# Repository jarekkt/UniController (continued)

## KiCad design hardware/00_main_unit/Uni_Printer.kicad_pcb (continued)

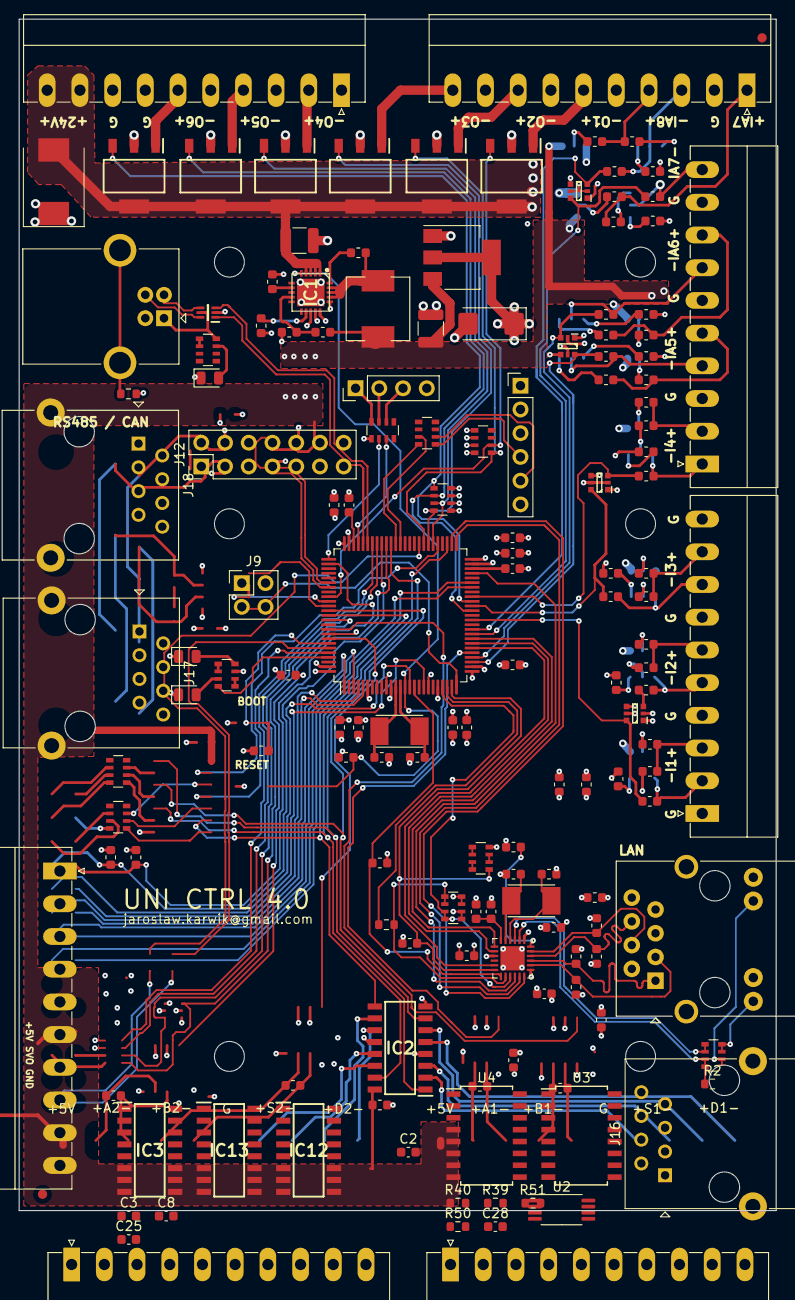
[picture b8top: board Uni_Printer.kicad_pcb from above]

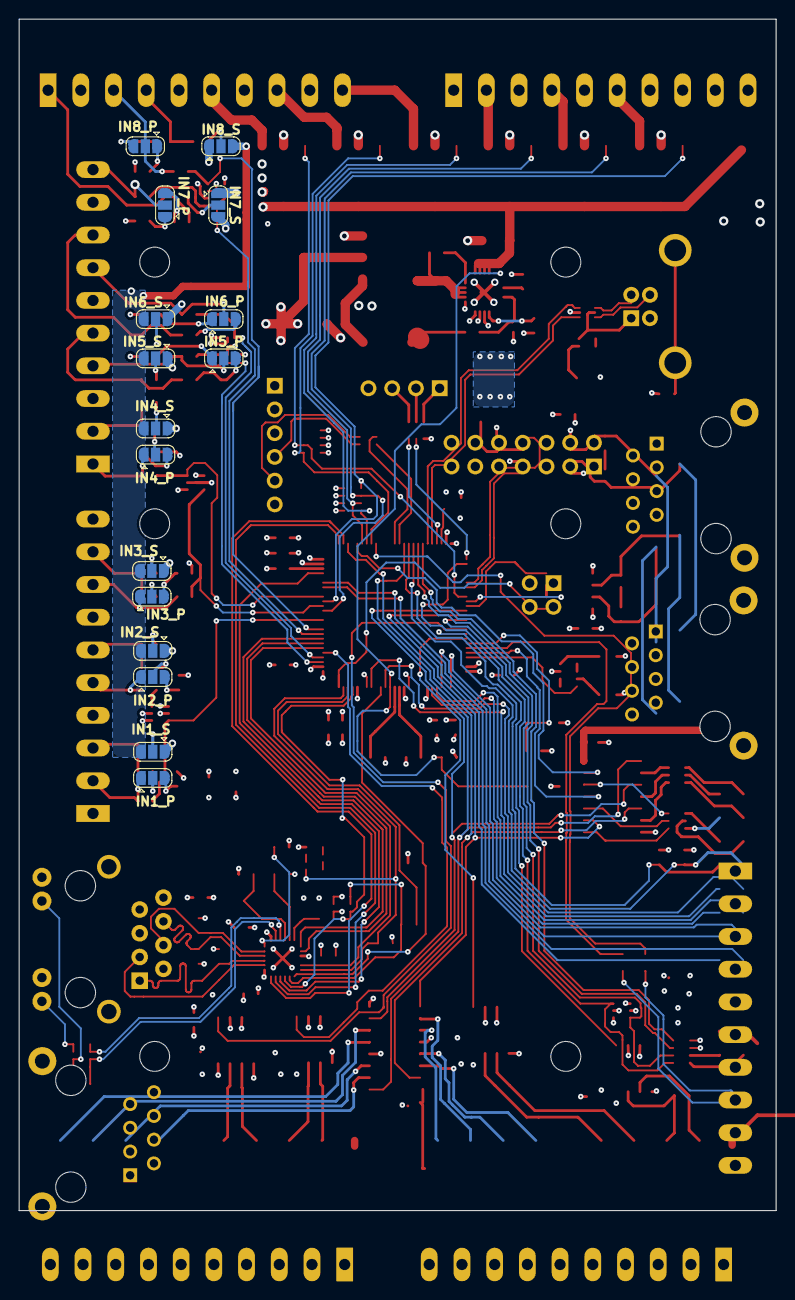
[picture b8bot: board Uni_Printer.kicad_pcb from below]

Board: 4 copper layers, 81.0 x 127.5 mm, 173 parts (16 on the bottom side), 202 nets.

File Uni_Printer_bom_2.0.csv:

Component,Description,Part,References,Value,Footprint,Quantity Per PCB,Datasheet,TME,Category,Mouser Price/Stock,Mouser Part Number,Manufacturer_Name,Height,RS Price/Stock,RS Part Number,Manufacturer_Part_Number,Arrow Part Number,Arrow Price/Stock,TME-WTYK,TME-GNIAZDO,Digi,MFG num
1,,C-Device,C4 C5 C18 C19,18pF,C_0603_1608Metric,4,~,VJ0603A180JXACW2BC,,,,,,,,,,,,,,
2,Unpolarized capacitor,C,C6 C7,18p,C_0603_1608Metric,2,~,,,,,,,,,,,,,,,
3,"Unpolarized capacitor, small symbol",C_Small,C42,5.6nF,C_0603_1608Metric,1,~,,,,,,,,,,,,,,,
4,"Unpolarized capacitor, small symbol",C_Small,C1 C21 C33 C35 C36 C37,100nF,C_0603_1608Metric,6,~,,,,,,,,,,,,,,,
5,,C-Device,C12 C14 C15 C16 C17 C20 C22 C24 C26 C31,100n,C_0603_1608Metric,10,~,C0603C104K3RAC,,,,,,,,,,,,,,
6,,C,C2 C3,100n,C_0603_1608Metric,2,,,Capacitor,,,,,,,,,,,,,
7,,C_Small-Device,C25 C27 C28 C29 C30 C34,100n,C_0603_1608Metric,6,~,C0603C104K3RAC WF06P-120R-5%,,,,,,,,,,,,,,
8,,C_Small-Sensor_tank_v1-rescue-Uni_General_v1-rescue-Uni_Printer_v1-rescue,C32,100n,C_0603_1608Metric,1,,C0603C104K3RAC,,,,,,,,,,,,,,
9,"Unpolarized capacitor, small symbol",C_Small,C41,2.2uF,C_0603_1608Metric,1,~,,,,,,,,,,,,,,,
10,,C-Device,C8 C10 C11 C13 C23 C38,10uF,C_1206_3216Metric,6,~,0805X106K100CT,,,,,,,,,,,,,,
11,"Unpolarized capacitor, small symbol",C_Small,C9,10uF,C_0603_1608Metric,1,~,,,,,,,,,,,,,,,
12,"Unpolarized capacitor, small symbol",C_Small,C44,100uF 6.3V Tantal,CP_EIA-6032-28_Kemet-C,1,~,,,,,,,,,,,,,,,
13,"Unpolarized capacitor, small symbol",C_Small,C40,10uF 50V,C_1210_3225Metric,1,~,,,,,,,,,,,,,,,
14,"Unpolarized capacitor, small symbol",C_Small,C43,22uF 25V,C_1206_3216Metric,1,~,,,,,,,,,,,,,,,
15,"Polarized capacitor, US symbol",CP1,CP1,1.0uF/1.0ESR,C_0603_1608Metric,1,~,,,,,,,,,,,,,,,
16,"Polarized capacitor, US symbol",CP1,CP2,470pF,C_0603_1608Metric,1,~,,,,,,,,,,,,,,,
17,,D_Schottky_x4_BAV99S-RESCUE-step2cnc-Sensor_tank_v1-rescue-Uni_General_v1-rescue-Uni_Printer_v1-rescue,D1 D4 D5 D7 D8,D_Schottky_x4_BAV99S,SOT-363,5,,BAV99S.115,,,,,,,,,,,,,,
18,,LED-Sensor_tank_v1-rescue-Uni_General_v1-rescue-Uni_Printer_v1-rescue,D2 D3 D9,LED,LED_0805_2012Metric,3,,,,,,,,,,,,,,,,
19,,NUF2042XV6T1G,D6,NUF2042XV6T1G,SOT50P160X60-6N,1,~,,,,,,,,,,,,,,,
20,Bidirectional transient-voltage-suppression diode,D_TVS,D10,SMCJ24CA,D_SMC,1,~,SMCJ24CA,,,,,,,,,,,,,,
21,,74*14-step2cnc-Uni_Printer_v1-rescue,IC3,74HC14D,SO14,1,~,,,,,,,,,,,,,,,
22,,AM26C31CD-AM26C31CD-Uni_Printer_v1-rescue,IC2,AM26C31CD,SOIC127P600X175-16N,1,http://www.ti.com/lit/ds/symlink/am26c31.pdf,,,https://www.mouser.com/Search/Refine.aspx?Keyword=595-AM26C31CD,595-AM26C31CD,Texas Instruments,1.75,http://uk.rs-online.com/web/p/products/5170520P,5170520P,AM26C31CD,,,,,,
23,,ITS4141NHUMA1,IC6 IC7 IC8 IC9 IC10 IC11,ITS4141NHUMA1,SOT230P700X170-4N,6,http://www.farnell.com/datasheets/8560http://www.infineon.co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,,,https://www.mouser.co.uk/ProductDetail/Infineon-Technologies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,726-ITS4141NHUMA1,Infineon,1.7,,,ITS4141NHUMA1,ITS4141NHUMA1,https://www.arrow.com/en/products/its4141nhuma1/infineon-tec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,,,,
24,,LAN8720A,IC5,LAN8742A,QFN-24-1EP_4x4mm_P0.5mm_EP2.6x2.6mm,1,,,,,,,,,,,,,,,,
25,,MAX17503ATP+,IC1,MAX17503ATP+,QFN50P400X400X80-21N,1,https://pdfserv.maximintegrated.com/en/ds/MAX17503.pdf,,,https://www.mouser.com/Search/Refine.aspx?Keyword=700-MAX175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,700-MAX17503ATP+,Maxim Integrated,0.8,,,MAX17503ATP+,,,,,,
26,,LM1117-step2cnc-Sensor_tank_v1-rescue-Uni_General_v1-rescue-Uni_Printer_v1-rescue-Uni_Printer-rescue,IC4,TLV1117-33,SOT-223-3_TabPin2,1,,TLV1117-33CDCYG3,,,,,,,,,,,,,,
27,"Generic connector, single row, 01x04, script generated (kicad-library-utils/schlib/autogen/connector/)",Conn_01x04_Male,J13,Conn_01x04_Male,PinHeader_1x04_P2.54mm_Vertical,1,~,,,,,,,,,,,,,,,
28,,Conn_01x10-Connector_Generic,J1 J2 J3 J4 J7 J8,Conn_01x10,PhoenixContact_MC-G_10x3.50mm_Angled,6,~,,,,,,,,,,,,15EDGK-3.5/10P,15EDGRC-3.5/10P,,
29,"Generic connector, double row, 02x14, odd/even pin numbering scheme (row 1 odd numbers, row 2 even numbers), script generated (kicad-library-utils/schlib/autogen/connector/)",Conn_02x14_Odd_Even,J14,Conn_02x13_Odd_Even,PinHeader_2x14_P2.54mm_Vertical,1,~,,,,,,,,,,,,,,,
30,,RJ45-TRANSFO_v2-rj12,J11,LMJ1998824110DL1T39J,LMJ1998824110DL1T39J,1,,RJ45-TRAFO-L,,,,,,,,,,,,,,
31,"RJ connector, 8P8C (8 positions 8 connected)",RJ45,J9 J12,RJ45,RJ45_Amphenol_54602-x08_Horizontal,2,~,,,,,,,,,,,,,,,
32,,USB_B-Connector,J10,USB B connector,USB_B_OST_USB-B1HSxx_Horizontal,1,~,TUEB4F2D0B,,,,,,,,,,,,,,
33,,Jumper_3_Bridged12-Jumper,JP1 JP2 JP3 JP4 JP7 JP8 JP9 JP10 JP11 JP12 JP13 JP14 JP15 JP16 JP17 JP18,Jumper,SolderJumper-3_P1.3mm_Bridged2Bar12_RoundedPad1.0x1.5mm,16,~,WF06P-120R-5%,,,,,,,,,,,,,,
34,,Jumper_NO_Small-Device,JP5 JP6,Jumper,SolderJumper-2_P1.3mm_Open_RoundedPad1.0x1.5mm,2,~,,,,,,,,,,,,,,,
35,,INDUCTOR_SMALL,L1,10uH,L_0603_1608Metric,1,,,,,,,,,,,,,,,,
36,"Inductor, small symbol",L_Small,L2,10uH,HPI0630,1,~,HPI0630-100,,,,,,,,,,,,,,
37,,R-Sensor_tank_v1-rescue-Uni_General_v1-rescue-Uni_Printer_v1-rescue,R49,0R,R_0603_1608Metric,1,~,WF06P-120R-5%,,,,,,,,,,,,,,
38,,R-RESCUE-step2cnc8_,R1,33,R_0603_1608Metric,1,~,,,,,,,,,,,,,,,
39,,R-RESCUE-step2cnc8_,R45 R46 R47 R48,49R9,R_0603_1608Metric,4,~,,,,,,,,,,,,,,,
40,,R-Sensor_tank_v1-rescue-Uni_General_v1-rescue-Uni_Printer_v1-rescue,R8 R12 R16 R20 R28 R32 R36 R39 R40 R43,120R,R_0603_1608Metric,10,,CRCW06030000Z0TABC WF06P-120R-5%,,,,,,,,,,,,,,
41,,R-Device,R22 R23 R24 R25,120R,R_0603_1608Metric,4,~,WF06P-120R-5%,,,,,,,,,,,,,,
42,,R-Sensor_tank_v1-rescue-Uni_General_v1-rescue-Uni_Printer_v1-rescue,R6 R10 R14 R18 R27 R31 R35 R42,1k,R_0603_1608Metric,8,,HP03-1K5% WF06P-120R-5%,,,,,,,,,,,,,,
43,,R-Device,R3 R4 R5,2k2,R_0603_1608Metric,3,~,HP03-2K25%,,,,,,,,,,,,,,
44,,R-Sensor_tank_v1-rescue-Uni_General_v1-rescue-Uni_Printer_v1-rescue,R7 R9 R11 R13 R15 R17 R19 R21 R26 R29 R30 R33 R34 R37 R41 R44,10k,R_0603_1608Metric,16,,SMD0603-680R-1% WF06P-120R-5%,,,,,,,,,,,,,,
45,,R-RESCUE-step2cnc8_,R38,12k1,R_0603_1608Metric,1,~,,,,,,,,,,,,,,,
46,"Resistor, small symbol",R_Small,R53,39k,R_0603_1608Metric,1,~,,,,,,,,,,,,,,,
47,"Resistor, small symbol",R_Small,R52,178k,R_0603_1608Metric,1,~,,,,,,,,,,,,,,,
48,,R_Pack04-Device,RN1 RN4 RN5 RN6 RN7 RN8 RN9,100R,R_Array_Convex_4x0603,7,~,DR1206-390K-4/8,,,,,,,,,,,,,,
49,"4 resistor network, parallel topology",R_Pack04,RN2,10k,R_Array_Convex_4x0603,1,~,,,,,,,,,,,,,,,
50,,R_Pack04-Device,RN12 RN13,15k,R_Array_Convex_4x0603,2,~,,,,,,,,,,,,,,,
51,"4 resistor network, parallel topology",R_Pack04,RN3 RN10,390R,R_Array_Convex_4x0603,2,~,,,,,,,,,,,,,,,
52,,SW_Push-Switch,SW2 SW3,SW_Push,SW_SPST_B3U-1000P,2,,B3U-1000PM,,,,,,,,,,,,,,
53,,ST1480ACDR-Sensor_tank_v1-rescue-Uni_General_v1-rescue-Uni_Printer_v1-rescue,U5 U6 U7 U8 U9,ST1480ACDR,SOIC-8_3.9x4.9mm_P1.27mm,5,,SP3077EEN-L SP3485EN-L,,,,,,,,,,,,,,
54,,STM32H743VITx,U1,STM32H743VITx,LQFP-100_14x14mm_P0.5mm,1,,,,,,,,,,,,,,,,
55,,TLE9251VSJ,U3,TLE9251VSJ,SOIC-8_3.9x4.9mm_P1.27mm,1,,,Driver,,,,,,,,,,,,TLE9251VSJXUMA1TR-ND,TLE9251VSJ
56,,Crystal-Device,Y2,ABM7-25.000MHZ-D2Y-T,XTAL500X320X130N_v2,1,~,ABM7-25.000MHZ-D2Y,,,,,,,,,,,,,,
57,,Crystal-Device,Y1,ABM7-8.000MHZ-D2Y-T,XTAL500X320X130N_v2,1,~,ABM7-8.000MHZ-D2Y,,,,,,,,,,,,,,





Component Groups:,57
Component Count:,171
Fitted Components:,171
Number of PCBs:,1
Total components:,171
Schematic Version:,2.0
Schematic Date:,2020-04-30
PCB Variant:,default
BoM Date:,14.01.2021 11:15:03
Schematic Source:,Uni_Printer.kicad_sch
KiCad Version:,Eeschema (5.99.0-7794-gffe7d2ea49)

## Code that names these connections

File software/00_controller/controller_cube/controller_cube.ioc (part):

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Mcu.Name=STM32H743VITx
Mcu.Package=LQFP100
Mcu.UserName=STM32H743VITx
PA0.GPIOParameters=PinState,GPIO_Label
PA0.GPIO_Label=ENET_RST
PA0.PinState=GPIO_PIN_SET
PA0.Signal=GPIO_Output
PA1.GPIOParameters=GPIO_Speed
PA1.GPIO_Speed=GPIO_SPEED_FREQ_VERY_HIGH
PA1.Mode=RMII
PA1.Signal=ETH_REF_CLK
PA10.Mode=Asynchronous
PA10.Signal=USART1_RX
PA11.GPIOParameters=GPIO_Label
PA11.GPIO_Label=IO_CPU7
PA11.Signal=GPIO_Input
PA12.GPIOParameters=GPIO_Label
PA12.GPIO_Label=OUT_CPU8
PA12.Signal=GPIO_Output
PA13\ (JTMS/SWDIO).Mode=Serial_Wire
PA13\ (JTMS/SWDIO).Signal=DEBUG_JTMS-SWDIO
PA14\ (JTCK/SWCLK).Mode=Serial_Wire
PA14\ (JTCK/SWCLK).Signal=DEBUG_JTCK-SWCLK
PA15\ (JTDI).GPIOParameters=GPIO_Label
PA15\ (JTDI).GPIO_Label=ENC3_PWM_CH1
PA15\ (JTDI).Signal=S_TIM2_CH1_ETR
PA2.GPIOParameters=GPIO_Speed
PA2.GPIO_Speed=GPIO_SPEED_FREQ_HIGH
PA2.Mode=RMII
PA2.Signal=ETH_MDIO
PA3.GPIOParameters=GPIO_Label
PA3.GPIO_Label=OUT_CPU3_PWM
PA3.Signal=S_TIM5_CH4
PA4.GPIOParameters=GPIO_Label
PA4.GPIO_Label=DAC_CPU
PA4.Signal=COMP_DAC11_group
PA5.GPIOParameters=GPIO_PuPd,GPIO_Label
PA5.GPIO_Label=IN_CPU7
PA5.GPIO_PuPd=GPIO_PULLDOWN
PA5.Signal=GPIO_Input
PA6.GPIOParameters=GPIO_Label
PA6.GPIO_Label=ENC1_CH1
PA6.Signal=S_TIM3_CH1
PA7.GPIOParameters=GPIO_Speed
PA7.GPIO_Speed=GPIO_SPEED_FREQ_VERY_HIGH
PA7.Mode=RMII
PA7.Signal=ETH_CRS_DV
PA8.GPIOParameters=GPIO_Label
PA8.GPIO_Label=I2C3_SCL
PA8.Mode=I2C
PA8.Signal=I2C3_SCL
PA9.Mode=Asynchronous
PA9.Signal=USART1_TX
PB0.GPIOParameters=GPIO_PuPd,GPIO_Label
PB0.GPIO_Label=IN_CPU8
PB0.GPIO_PuPd=GPIO_PULLDOWN
PB0.Signal=GPIO_Input
PB1.GPIOParameters=GPIO_PuPd,GPIO_Label
PB1.GPIO_Label=IN_CPU9
PB1.GPIO_PuPd=GPIO_PULLDOWN
PB1.Signal=GPIO_Input
PB10.Mode=Single Bank 1
PB10.Signal=QUADSPI_BK1_NCS
PB11.GPIOParameters=GPIO_Speed
PB11.GPIO_Speed=GPIO_SPEED_FREQ_VERY_HIGH
PB11.Mode=RMII
PB11.Signal=ETH_TX_EN
PB12.GPIOParameters=GPIO_Speed
PB12.GPIO_Speed=GPIO_SPEED_FREQ_VERY_HIGH
PB12.Mode=RMII
PB12.Signal=ETH_TXD0
PB13.GPIOParameters=GPIO_Speed
PB13.GPIO_Speed=GPIO_SPEED_FREQ_VERY_HIGH
PB13.Mode=RMII
PB13.Signal=ETH_TXD1
PB14.Signal=S_TIM12_CH1
PB15.GPIOParameters=GPIO_Label
PB15.GPIO_Label=IO_CPU9
PB15.Signal=GPIO_Input
PB2.Mode=Single Bank 1
PB2.Signal=QUADSPI_CLK
PB3\ (JTDO/TRACESWO).GPIOParameters=GPIO_Label
PB3\ (JTDO/TRACESWO).GPIO_Label=ENC_PWM_CH2
PB3\ (JTDO/TRACESWO).Signal=S_TIM2_CH2
PB4\ (NJTRST).GPIOParameters=GPIO_Label
PB4\ (NJTRST).GPIO_Label=IO_CPU6
PB4\ (NJTRST).Signal=GPIO_Input
PB5.GPIOParameters=GPIO_Label
PB5.GPIO_Label=ENC1_CH2
PB5.Signal=S_TIM3_CH2
PB6.GPIOParameters=GPIO_Label
PB6.GPIO_Label=ENC2_CH1
PB6.Signal=S_TIM4_CH1
PB7.GPIOParameters=GPIO_Label
PB7.GPIO_Label=ENC2_CH2
PB7.Signal=S_TIM4_CH2
PB8.GPIOParameters=GPIO_Label
PB8.GPIO_Label=IO_CPU5
PB8.Signal=GPIO_Input
PB9.GPIOParameters=GPIO_Label
PB9.GPIO_Label=OUT_STEP3
PB9.Signal=S_TIM17_CH1
PC0.Signal=ADCx_INP10
PC1.GPIOParameters=GPIO_Speed
PC1.GPIO_Speed=GPIO_SPEED_FREQ_HIGH
PC1.Mode=RMII
PC1.Signal=ETH_MDC
PC10.GPIOParameters=GPIO_Label
PC10.GPIO_Label=LED
PC10.Signal=GPIO_Output
PC11.GPIOParameters=GPIO_Label
PC11.GPIO_Label=OUT_RS485_RE
PC11.Signal=GPIO_Output
PC12.GPIOParameters=GPIO_Label
PC12.GPIO_Label=IO_CPU4
PC12.Signal=GPIO_Input
PC13.GPIOParameters=GPIO_PuPd,GPIO_Label
PC13.GPIO_Label=IN_CPU6
PC13.GPIO_PuPd=GPIO_PULLDOWN
PC13.Signal=GPIO_Input
PC14-OSC32_IN\ (OSC32_IN).GPIOParameters=GPIO_PuPd,GPIO_Label
PC14-OSC32_IN\ (OSC32_IN).GPIO_Label=IN_CPU5
PC14-OSC32_IN\ (OSC32_IN).GPIO_PuPd=GPIO_PULLDOWN
PC14-OSC32_IN\ (OSC32_IN).Signal=GPIO_Input
PC15-OSC32_OUT\ (OSC32_OUT).GPIOParameters=GPIO_PuPd,GPIO_Label
PC15-OSC32_OUT\ (OSC32_OUT).GPIO_Label=IN_CPU4
PC15-OSC32_OUT\ (OSC32_OUT).GPIO_PuPd=GPIO_PULLDOWN
PC15-OSC32_OUT\ (OSC32_OUT).Signal=GPIO_Input
PC2_C.GPIOParameters=GPIO_Label
PC2_C.GPIO_Label=IO_CPU3
PC2_C.Signal=GPIO_Input
PC3_C.GPIOParameters=GPIO_Label
PC3_C.GPIO_Label=ADC_CH2
PC3_C.Mode=IN1-Single-Ended
PC3_C.Signal=ADC3_INP1
PC4.GPIOParameters=GPIO_Speed
PC4.GPIO_Speed=GPIO_SPEED_FREQ_VERY_HIGH
PC4.Mode=RMII
PC4.Signal=ETH_RXD0
PC5.GPIOParameters=GPIO_Speed
PC5.GPIO_Speed=GPIO_SPEED_FREQ_VERY_HIGH
PC5.Mode=RMII
PC5.Signal=ETH_RXD1
PC6.Mode=Asynchronous
PC6.Signal=USART6_TX
PC7.Mode=Asynchronous
PC7.Signal=USART6_RX
PC8.GPIOParameters=GPIO_Label
PC8.GPIO_Label=OUT_STEP1
PC8.Signal=S_TIM8_CH3
PC9.GPIOParameters=GPIO_Label
PC9.GPIO_Label=I2C3_SDA
PC9.Mode=I2C
PC9.Signal=I2C3_SDA
PD0.Mode=FDCAN_Activate
PD0.Signal=FDCAN1_RX
PD1.Mode=FDCAN_Activate
PD1.Signal=FDCAN1_TX
PD10.GPIOParameters=GPIO_Label
PD10.GPIO_Label=OUT_CPU5
PD10.Signal=GPIO_Output
PD11.Mode=Single Bank 1
PD11.Signal=QUADSPI_BK1_IO0
PD12.Mode=Single Bank 1
PD12.Signal=QUADSPI_BK1_IO1
PD13.Mode=Single Bank 1
PD13.Signal=QUADSPI_BK1_IO3
PD14.GPIOParameters=GPIO_Label
PD14.GPIO_Label=OUT_DIR4
PD14.Signal=GPIO_Output
PD15.GPIOParameters=GPIO_Label
PD15.GPIO_Label=OUT_STEP5
PD15.Signal=GPIO_Output
PD2.GPIOParameters=GPIO_Label
PD2.GPIO_Label=OUT_STEP7
PD2.Signal=GPIO_Output
PD3.GPIOParameters=GPIO_Label
PD3.GPIO_Label=OUT_CPU7
PD3.Signal=GPIO_Output
PD4.GPIOParameters=GPIO_Label
PD4.GPIO_Label=IO_CPU8
PD4.Signal=GPIO_Input
PD5.GPIOParameters=GPIO_Label
PD5.GPIO_Label=OUT_DIR7
PD5.Signal=GPIO_Output
PD6.GPIOParameters=GPIO_Label
PD6.GPIO_Label=OUT_DIR1
PD6.Signal=GPIO_Output
PD7.GPIOParameters=GPIO_Label
PD7.GPIO_Label=OUT_DIR2
PD7.Signal=GPIO_Output
PD8.GPIOParameters=GPIO_Label
PD8.GPIO_Label=OUT_DIR3
PD8.Signal=GPIO_Output
PD9.GPIOParameters=GPIO_Label
PD9.GPIO_Label=OUT_CPU6
PD9.Signal=GPIO_Output
PE0.GPIOParameters=GPIO_Label
PE0.GPIO_Label=IO_CPU2
PE0.Signal=GPIO_Input
PE1.GPIOParameters=GPIO_PuPd,GPIO_Label
PE1.GPIO_Label=IN_CPU10
PE1.GPIO_PuPd=GPIO_PULLDOWN
PE1.Signal=GPIO_Input
PE10.GPIOParameters=GPIO_Label
PE10.GPIO_Label=OUT_DIR5
PE10.Signal=GPIO_Output
PE11.GPIOParameters=GPIO_Label
PE11.GPIO_Label=OUT_CPU2_PWM
PE11.Signal=S_TIM1_CH2
PE12.GPIOParameters=GPIO_Label
PE12.GPIO_Label=OUT_STEP6
PE12.Signal=GPIO_Output
PE13.GPIOParameters=GPIO_Label
PE13.GPIO_Label=OUT_STEP4
PE13.Signal=GPIO_Output
PE14.GPIOParameters=GPIO_Label
PE14.GPIO_Label=OUT_CPU4_PWM
PE14.Signal=S_TIM1_CH4
PE15.GPIOParameters=GPIO_Label
PE15.GPIO_Label=OUT_DIR6
PE15.Signal=GPIO_Output
PE2.Mode=Single Bank 1
PE2.Signal=QUADSPI_BK1_IO2
PE3.GPIOParameters=GPIO_Label
PE3.GPIO_Label=IO_CPU1
PE3.Signal=GPIO_Input
PE4.GPIOParameters=GPIO_PuPd,GPIO_Label
PE4.GPIO_Label=IN_CPU2
PE4.GPIO_PuPd=GPIO_PULLDOWN
PE4.Signal=GPIO_Input
PE5.GPIOParameters=GPIO_PuPd,GPIO_Label
PE5.GPIO_Label=IN_CPU1
PE5.GPIO_PuPd=GPIO_PULLDOWN
PE5.Signal=GPIO_Input
PE6.GPIOParameters=GPIO_PuPd,GPIO_Label
PE6.GPIO_Label=IN_CPU3
PE6.GPIO_PuPd=GPIO_PULLDOWN
PE6.Signal=GPIO_Input
PE7.GPIOParameters=GPIO_Label
PE7.GPIO_Label=OUT_CPU9
PE7.Signal=GPIO_Output
PE8.GPIOParameters=GPIO_Label
PE8.GPIO_Label=OUT_CPU10
PE8.Signal=GPIO_Output
PE9.GPIOParameters=GPIO_Label
PE9.GPIO_Label=OUT_CPU1_PWM
PE9.Signal=S_TIM1_CH1
PH0-OSC_IN\ (PH0).Mode=HSE-External-Oscillator
PH0-OSC_IN\ (PH0).Signal=RCC_OSC_IN
PH1-OSC_OUT\ (PH1).Mode=HSE-External-Oscillator
PH1-OSC_OUT\ (PH1).Signal=RCC_OSC_OUT
RCC.HSE_VALUE=25000000
RCC.SYSCLKFreq_VALUE=480000000
RCC.SYSCLKSource=RCC_SYSCLKSOURCE_PLLCLK
board=custom

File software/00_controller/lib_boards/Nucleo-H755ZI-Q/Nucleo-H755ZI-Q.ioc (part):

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Mcu.Name=STM32H755ZITx
Mcu.Package=LQFP144
Mcu.UserName=STM32H755ZITx
PA0.GPIOParameters=GPIO_Label,PinAttribute
PA0.GPIO_Label=OUT3_LED_UP_T2C1
PA0.PinAttribute=CortexM7
PA0.Signal=S_TIM2_CH1_ETR
PA1.GPIOParameters=PinAttribute
PA1.Mode=RMII
PA1.PinAttribute=CortexM7
PA1.Signal=ETH_REF_CLK
PA11.GPIOParameters=PinAttribute
PA11.Mode=Device_Only
PA11.PinAttribute=CortexM7
PA11.Signal=USB_OTG_FS_DM
PA12.GPIOParameters=PinAttribute
PA12.Mode=Device_Only
PA12.PinAttribute=CortexM7
PA12.Signal=USB_OTG_FS_DP
PA2.GPIOParameters=PinAttribute
PA2.Mode=RMII
PA2.PinAttribute=CortexM7
PA2.Signal=ETH_MDIO
PA3.GPIOParameters=GPIO_Label,PinAttribute
PA3.GPIO_Label=ANA1
PA3.PinAttribute=CortexM7
PA3.Signal=ADCx_INP15
PA6.ContextOwner=CortexM7
PA6.GPIOParameters=GPIO_Label,PinAttribute
PA6.GPIO_Label=OUT9_SPARE3
PA6.PinAttribute=CortexM7
PA6.Signal=GPIO_Output
PA7.GPIOParameters=PinAttribute
PA7.Mode=RMII
PA7.PinAttribute=CortexM7
PA7.Signal=ETH_CRS_DV
PA8.GPIOParameters=PinAttribute
PA8.PinAttribute=CortexM7
PA8.Signal=USB_OTG_FS_SOF
PA9.GPIOParameters=PinAttribute
PA9.Mode=Activate_VBUS
PA9.PinAttribute=CortexM7
PA9.Signal=USB_OTG_FS_VBUS
PB0.Signal=GPIO_Output
PB1.ContextOwner=CortexM7
PB1.GPIOParameters=GPIO_Label,PinAttribute
PB1.GPIO_Label=IN2_Y_MIN
PB1.PinAttribute=CortexM7
PB1.Signal=GPIO_Input
PB10.GPIOParameters=GPIO_Label,PinAttribute
PB10.GPIO_Label=OUT6_PUMP_PRESS_T2C3
PB10.PinAttribute=CortexM7
PB10.Signal=S_TIM2_CH3
PB11.GPIOParameters=GPIO_Label,PinAttribute
PB11.GPIO_Label=OUT5_PUMP_VACUUM_T2C4
PB11.PinAttribute=CortexM7
PB11.Signal=S_TIM2_CH4
PB13.GPIOParameters=PinAttribute
PB13.Mode=RMII
PB13.PinAttribute=CortexM7
PB13.Signal=ETH_TXD1
PB14.ContextOwner=CortexM7
PB14.GPIOParameters=PinAttribute
PB14.PinAttribute=CortexM7
PB14.Signal=GPIO_Output
PB6.GPIOParameters=GPIO_Label,PinAttribute
PB6.GPIO_Label=TX_XYW
PB6.Mode=Asynchronous
PB6.PinAttribute=CortexM7
PB6.Signal=USART1_TX
PB7.GPIOParameters=GPIO_Label,PinAttribute
PB7.GPIO_Label=RX_XYW
PB7.Mode=Asynchronous
PB7.PinAttribute=CortexM7
PB7.Signal=USART1_RX
PC0.GPIOParameters=GPIO_Label,PinAttribute
PC0.GPIO_Label=ANA2
PC0.PinAttribute=CortexM7
PC0.Signal=ADCx_INP10
PC1.GPIOParameters=PinAttribute
PC1.Mode=RMII
PC1.PinAttribute=CortexM7
PC1.Signal=ETH_MDC
PC13.ContextOwner=CortexM7
PC13.GPIOParameters=PinAttribute
PC13.PinAttribute=CortexM7
PC13.Signal=GPIO_Input
PC14-OSC32_IN\ (OSC32_IN).GPIOParameters=PinAttribute
PC14-OSC32_IN\ (OSC32_IN).PinAttribute=Free
PC14-OSC32_IN\ (OSC32_IN).Signal=RCC_OSC32_IN
PC15-OSC32_OUT\ (OSC32_OUT).GPIOParameters=PinAttribute
PC15-OSC32_OUT\ (OSC32_OUT).PinAttribute=Free
PC15-OSC32_OUT\ (OSC32_OUT).Signal=RCC_OSC32_OUT
PC2_C.ContextOwner=CortexM7
PC2_C.GPIOParameters=GPIO_Label,PinAttribute
PC2_C.GPIO_Label=IN3_Z_MIN
PC2_C.PinAttribute=CortexM7
PC2_C.Signal=GPIO_Input
PC3_C.ContextOwner=CortexM7
PC3_C.GPIOParameters=GPIO_Label,PinAttribute
PC3_C.GPIO_Label=IN1_X_MIN
PC3_C.PinAttribute=CortexM7
PC3_C.Signal=GPIO_Input
PC4.GPIOParameters=PinAttribute
PC4.Mode=RMII
PC4.PinAttribute=CortexM7
PC4.Signal=ETH_RXD0
PC5.GPIOParameters=PinAttribute
PC5.Mode=RMII
PC5.PinAttribute=CortexM7
PC5.Signal=ETH_RXD1
PC6.GPIOParameters=GPIO_Label,PinAttribute
PC6.GPIO_Label=ENC1_T3C1
PC6.PinAttribute=CortexM7
PC6.Signal=S_TIM3_CH1
PC7.GPIOParameters=GPIO_Label,PinAttribute
PC7.GPIO_Label=ENC1_T3C2
PC7.PinAttribute=CortexM7
PC7.Signal=S_TIM3_CH2
PD0.GPIOParameters=GPIO_Label,PinAttribute
PD0.GPIO_Label=CAN_RX
PD0.Mode=FDCAN_Activate
PD0.PinAttribute=CortexM7
PD0.Signal=FDCAN1_RX
PD1.GPIOParameters=GPIO_Label,PinAttribute
PD1.GPIO_Label=CAN_TX
PD1.Mode=FDCAN_Activate
PD1.PinAttribute=CortexM7
PD1.Signal=FDCAN1_TX
PD10.ContextOwner=CortexM7
PD10.GPIOParameters=GPIO_Label,PinAttribute
PD10.GPIO_Label=USB_OTG_FS_PWR_EN
PD10.PinAttribute=CortexM7
PD10.Signal=GPIO_Output
PD12.GPIOParameters=GPIO_Label,PinAttribute
PD12.GPIO_Label=ENC2_T4C1
PD12.PinAttribute=CortexM7
PD12.Signal=S_TIM4_CH1
PD13.GPIOParameters=GPIO_Label,PinAttribute
PD13.GPIO_Label=ENC2_T4C2
PD13.PinAttribute=CortexM7
PD13.Signal=S_TIM4_CH2
PD14.ContextOwner=CortexM7
PD14.GPIOParameters=GPIO_Label,PinAttribute
PD14.GPIO_Label=OUT7_SAPRE1
PD14.PinAttribute=CortexM7
PD14.Signal=GPIO_Output
PD15.ContextOwner=CortexM7
PD15.GPIOParameters=GPIO_Label,PinAttribute
PD15.GPIO_Label=OUT8_SPARE2
PD15.PinAttribute=CortexM7
PD15.Signal=GPIO_Output
PD3.ContextOwner=CortexM7
PD3.GPIOParameters=GPIO_Label,PinAttribute
PD3.GPIO_Label=DIR_Y
PD3.PinAttribute=CortexM7
PD3.Signal=GPIO_Output
PD4.ContextOwner=CortexM7
PD4.GPIOParameters=GPIO_Label,PinAttribute
PD4.GPIO_Label=STEP_Y
PD4.PinAttribute=CortexM7
PD4.Signal=GPIO_Output
PD5.GPIOParameters=GPIO_Label,PinAttribute
PD5.GPIO_Label=TX_UVZ
PD5.Mode=Asynchronous
PD5.PinAttribute=CortexM7
PD5.Signal=USART2_TX
PD6.GPIOParameters=GPIO_Label,PinAttribute
PD6.GPIO_Label=RX_UVZ
PD6.Mode=Asynchronous
PD6.PinAttribute=CortexM7
PD6.Signal=USART2_RX
PD7.ContextOwner=CortexM7
PD7.GPIOParameters=GPIO_Label,PinAttribute
PD7.GPIO_Label=IN4_ESTOP
PD7.PinAttribute=CortexM7
PD7.Signal=GPIO_Input
PD8.GPIOParameters=PinAttribute
PD8.Mode=Asynchronous
PD8.PinAttribute=CortexM7
PD8.Signal=USART3_TX
PD9.GPIOParameters=PinAttribute
PD9.Mode=Asynchronous
PD9.PinAttribute=CortexM7
PD9.Signal=USART3_RX
PE1.ContextOwner=CortexM7
PE1.GPIOParameters=PinAttribute
PE1.PinAttribute=CortexM7
PE1.Signal=GPIO_Output
PE10.ContextOwner=CortexM7
PE10.GPIOParameters=GPIO_Label,PinAttribute
PE10.GPIO_Label=DIR_V
PE10.PinAttribute=CortexM7
PE10.Signal=GPIO_Output
PE11.ContextOwner=CortexM7
PE11.GPIOParameters=GPIO_Label,PinAttribute
PE11.GPIO_Label=OUT1_VALVE2
PE11.PinAttribute=CortexM7
PE11.Signal=GPIO_Output
PE12.ContextOwner=CortexM7
PE12.GPIOParameters=GPIO_Label,PinAttribute
PE12.GPIO_Label=STEP_V
PE12.PinAttribute=CortexM7
PE12.Signal=GPIO_Output
PE13.GPIOParameters=GPIO_Label,PinAttribute
PE13.GPIO_Label=OUT4_LED_DN_T1C3
PE13.PinAttribute=CortexM7
PE13.Signal=S_TIM1_CH3
PE14.ContextOwner=CortexM7
PE14.GPIOParameters=GPIO_Label,PinAttribute
PE14.GPIO_Label=STEP_Z
PE14.PinAttribute=CortexM7
PE14.Signal=GPIO_Output
PE15.ContextOwner=CortexM7
PE15.GPIOParameters=GPIO_Label,PinAttribute
PE15.GPIO_Label=STEP_U
PE15.PinAttribute=CortexM7
PE15.Signal=GPIO_Output
PE3.ContextOwner=CortexM7
PE3.GPIOParameters=GPIO_Label,PinAttribute
PE3.GPIO_Label=OUT12_SPARE6
PE3.PinAttribute=CortexM7
PE3.Signal=GPIO_Output
PE6.ContextOwner=CortexM7
PE6.GPIOParameters=GPIO_Label,PinAttribute
PE6.GPIO_Label=DIR_U
PE6.PinAttribute=CortexM7
PE6.Signal=GPIO_Output
PE7.ContextOwner=CortexM7
PE7.GPIOParameters=GPIO_Label,PinAttribute
PE7.GPIO_Label=STEP_W
PE7.PinAttribute=CortexM7
PE7.Signal=GPIO_Output
PE8.ContextOwner=CortexM7
PE8.GPIOParameters=GPIO_Label,PinAttribute
PE8.GPIO_Label=DIR_W
PE8.PinAttribute=CortexM7
PE8.Signal=GPIO_Output
PF11.ContextOwner=CortexM7
PF11.GPIOParameters=GPIO_Label,PinAttribute
PF11.GPIO_Label=IN5_SPARE1
PF11.PinAttribute=CortexM7
PF11.Signal=GPIO_Input
PF6.ContextOwner=CortexM7
PF6.GPIOParameters=GPIO_Label,PinAttribute
PF6.GPIO_Label=IN6_SPARE2
PF6.PinAttribute=CortexM7
PF6.Signal=GPIO_Input
PF8.ContextOwner=CortexM7
PF8.GPIOParameters=GPIO_Label,PinAttribute
PF8.GPIO_Label=OUT11_SPARE5
PF8.PinAttribute=CortexM7
PF8.Signal=GPIO_Output
PF9.ContextOwner=CortexM7
PF9.GPIOParameters=GPIO_Label,PinAttribute
PF9.GPIO_Label=OUT10_SPARE4
PF9.PinAttribute=CortexM7
PF9.Signal=GPIO_Output
PG11.GPIOParameters=PinAttribute
PG11.Mode=RMII
PG11.PinAttribute=CortexM7
PG11.Signal=ETH_TX_EN
PG12.ContextOwner=CortexM7
PG12.GPIOParameters=GPIO_Label,PinAttribute
PG12.GPIO_Label=DIR_Z
PG12.PinAttribute=CortexM7
PG12.Signal=GPIO_Output
PG13.GPIOParameters=PinAttribute
PG13.Mode=RMII
PG13.PinAttribute=CortexM7
PG13.Signal=ETH_TXD0
PG14.ContextOwner=CortexM7
PG14.GPIOParameters=GPIO_Label,PinAttribute
PG14.GPIO_Label=TMC_ENA
PG14.PinAttribute=CortexM7
PG14.Signal=GPIO_Output
PG6.ContextOwner=CortexM7
PG6.GPIOParameters=GPIO_Label,PinAttribute
PG6.GPIO_Label=OUT2_VALVE1
PG6.PinAttribute=CortexM7
PG6.Signal=GPIO_Output
PG7.ContextOwner=CortexM7
PG7.GPIOParameters=GPIO_Label,PinAttribute
PG7.GPIO_Label=USB_OTG_FS_OVCR
PG7.PinAttribute=CortexM7
PG7.Signal=GPXTI7
PH0-OSC_IN\ (PH0).GPIOParameters=PinAttribute
PH0-OSC_IN\ (PH0).Mode=HSE-External-Clock-Source
PH0-OSC_IN\ (PH0).PinAttribute=Free
PH0-OSC_IN\ (PH0).Signal=RCC_OSC_IN
PH1-OSC_OUT\ (PH1).GPIOParameters=PinAttribute
PH1-OSC_OUT\ (PH1).PinAttribute=Free
PH1-OSC_OUT\ (PH1).Signal=RCC_OSC_OUT
RCC.HSE_VALUE=8000000
RCC.SYSCLKFreq_VALUE=480000000
RCC.SYSCLKSource=RCC_SYSCLKSOURCE_PLLCLK
board=NUCLEO-H755ZI-Q
boardIOC=true

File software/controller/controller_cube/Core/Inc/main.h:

/* USER CODE BEGIN Header */
/**
  ******************************************************************************
  * @file           : main.h
  * @brief          : Header for main.c file.
  *                   This file contains the common defines of the application.
  ******************************************************************************
  * @attention
  *
  * <h2><center>&copy; Copyright (c) 2020 STMicroelectronics.
  * All rights reserved.</center></h2>
  *
  * This software component is licensed by ST under Ultimate Liberty license
  * SLA0044, the "License"; You may not use this file except in compliance with
  * the License. You may obtain a copy of the License at:
  *                             www.st.com/SLA0044
  *
  ******************************************************************************
  */
/* USER CODE END Header */

/* Define to prevent recursive inclusion -------------------------------------*/
#ifndef __MAIN_H
#define __MAIN_H

#ifdef __cplusplus
extern "C" {
#endif

/* Includes ------------------------------------------------------------------*/
#include "stm32h7xx_hal.h"
#include "stm32h7xx_ll_usart.h"
#include "stm32h7xx_ll_rcc.h"
#include "stm32h7xx.h"
#include "stm32h7xx_ll_system.h"
#include "stm32h7xx_ll_gpio.h"
#include "stm32h7xx_ll_exti.h"
#include "stm32h7xx_ll_bus.h"
#include "stm32h7xx_ll_cortex.h"
#include "stm32h7xx_ll_utils.h"
#include "stm32h7xx_ll_pwr.h"
#include "stm32h7xx_ll_dma.h"

/* Private includes ----------------------------------------------------------*/
/* USER CODE BEGIN Includes */

/* USER CODE END Includes */

/* Exported types ------------------------------------------------------------*/
/* USER CODE BEGIN ET */

/* USER CODE END ET */

/* Exported constants --------------------------------------------------------*/
/* USER CODE BEGIN EC */

/* USER CODE END EC */

/* Exported macro ------------------------------------------------------------*/
/* USER CODE BEGIN EM */

/* USER CODE END EM */

/* Exported functions prototypes ---------------------------------------------*/
void Error_Handler(void);

/* USER CODE BEGIN EFP */

/* USER CODE END EFP */

/* Private defines -----------------------------------------------------------*/
#define WDG_KICK_Pin LL_GPIO_PIN_2
#define WDG_KICK_GPIO_Port GPIOE
#define ADDR2_Pin LL_GPIO_PIN_3
#define ADDR2_GPIO_Port GPIOE
#define ADDR3_Pin LL_GPIO_PIN_4
#define ADDR3_GPIO_Port GPIOE
#define OUT3_Pin LL_GPIO_PIN_0
#define OUT3_GPIO_Port GPIOC
#define OUT4_Pin LL_GPIO_PIN_1
#define OUT4_GPIO_Port GPIOC
#define ADC_S2_Pin LL_GPIO_PIN_3
#define ADC_S2_GPIO_Port GPIOC
#define IN1_Pin LL_GPIO_PIN_0
#define IN1_GPIO_Port GPIOA
#define IN2_Pin LL_GPIO_PIN_1
#define IN2_GPIO_Port GPIOA
#define IN3_Pin LL_GPIO_PIN_2
#define IN3_GPIO_Port GPIOA
#define IN4_Pin LL_GPIO_PIN_3
#define IN4_GPIO_Port GPIOA
#define IN_ADC1_Pin LL_GPIO_PIN_4
#define IN_ADC1_GPIO_Port GPIOA
#define IN_ADC2_Pin LL_GPIO_PIN_5
#define IN_ADC2_GPIO_Port GPIOA
#define IN_ADC3_Pin LL_GPIO_PIN_7
#define IN_ADC3_GPIO_Port GPIOA
#define IN_ADC4_Pin LL_GPIO_PIN_4
#define IN_ADC4_GPIO_Port GPIOC
#define ADC_S1_Pin LL_GPIO_PIN_5
#define ADC_S1_GPIO_Port GPIOC
#define OUT1_Pin LL_GPIO_PIN_0
#define OUT1_GPIO_Port GPIOB
#define OUT2_Pin LL_GPIO_PIN_1
#define OUT2_GPIO_Port GPIOB
#define LED_Pin LL_GPIO_PIN_12
#define LED_GPIO_Port GPIOE
#define REVISION_S1_Pin LL_GPIO_PIN_14
#define REVISION_S1_GPIO_Port GPIOE
#define REVISION_S2_Pin LL_GPIO_PIN_15
#define REVISION_S2_GPIO_Port GPIOE
#define USART3_CTRL_Pin LL_GPIO_PIN_12
#define USART3_CTRL_GPIO_Port GPIOB
#define LIGHT_ON_Pin LL_GPIO_PIN_8
#define LIGHT_ON_GPIO_Port GPIOD
#define OUT_EXT2_Pin LL_GPIO_PIN_10
#define OUT_EXT2_GPIO_Port GPIOD
#define OUT_EXT4_Pin LL_GPIO_PIN_12
#define OUT_EXT4_GPIO_Port GPIOD
#define OUT_EXT6_Pin LL_GPIO_PIN_14
#define OUT_EXT6_GPIO_Port GPIOD
#define CAN1_ENA_Pin LL_GPIO_PIN_9
#define CAN1_ENA_GPIO_Port GPIOC
#define ETH_INT_Pin LL_GPIO_PIN_10
#define ETH_INT_GPIO_Port GPIOC
#define ETH_RST_Pin LL_GPIO_PIN_3
#define ETH_RST_GPIO_Port GPIOD
#define USART2_CTRL_Pin LL_GPIO_PIN_7
#define USART2_CTRL_GPIO_Port GPIOD
#define ETH_CS_Pin LL_GPIO_PIN_4
#define ETH_CS_GPIO_Port GPIOB
#define I2C1_SCL_Pin LL_GPIO_PIN_8
#define I2C1_SCL_GPIO_Port GPIOB
#define I2C1_SDA_Pin LL_GPIO_PIN_9
#define I2C1_SDA_GPIO_Port GPIOB
#define ADDR0_Pin LL_GPIO_PIN_0
#define ADDR0_GPIO_Port GPIOE
#define ADDR1_Pin LL_GPIO_PIN_1
#define ADDR1_GPIO_Port GPIOE
/* USER CODE BEGIN Private defines */

/* USER CODE END Private defines */

#ifdef __cplusplus
}
#endif

#endif /* __MAIN_H */

/************************ (C) COPYRIGHT STMicroelectronics *****END OF FILE****/

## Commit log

2021-01-11 Files added
2021-01-13 UPDATE - LAN chipset waiting for verification
2021-01-14 UPDATE - LAN corrections
2021-01-19 UPDATE - Traces finished
2021-01-25 UPDATE - finished
2021-02-01 Fixes
2021-02-01 UPDATE - Uni_stick the rest of files
2021-02-04 Added software files - from previous prototype
2021-02-04 Changes in directories
2021-02-06 More updates toward new CPU
2021-02-07 Debug uart added
2021-02-17 UPDATE - 3D and Jumper descriptions
2021-02-17 Fixes after wrong merge
2021-02-17 UPDATE - stick
2021-02-17 Cleanup for new hardware version (not finished yet)
2021-02-18 Fixes before ordering PCB
2021-02-20 First succesful compilation for new hardware.
2021-02-20 More fixes for ethernet and USB
2021-02-21 More advanced test
2021-02-23 More splits in functionality
2021-02-24 Fixes for new hw version
2021-02-25 Test script modified
2021-03-01 More dev for network connection
2021-03-03 Fixes in net support
2021-03-07 Fixed new interface
2021-03-11 More updates to motion engine
2021-03-11 More fixes
2021-03-15 Ethernet runnning
2021-03-15 Error rounding fixed.
2021-03-23 More axis added
2021-04-01 Fixes in memory layout ( for eth DMA )
2021-04-05 Implementing missing gcode support
2021-04-06 Fixes in FreeRtos ocnfiguration and netowrking
2021-04-06 Fix in ethernet callbacks
2021-05-03 Fixes in networking
2021-12-07 Remote mode fixes
2021-12-30 IO changes for 7 axis
2022-01-01 Changes for new schmeatics - removed FDCAN and RS485
2022-01-07 FW and SW updates for new revision
2022-01-08 Fixes in ethernet and USB communication
2022-01-16 Fixed path calculation
2022-02-03 Real tests with OpewnPnp - fixes in gcode processor
2022-02-03 More tests with OpenPnp
2022-02-03 Fixed jerk calculations in Python
2022-06-14 New idea for controller - new hw principle
2022-06-19 Fixes in PCB
2022-06-19 More fixes in PCB
2022-06-19 Removed CAN and RS485 drivers
2022-06-20 Fixes in PCB design
2022-07-13 Prepared for first prototype
2022-07-29 Fixes after first power on - both software (ethernet reset) and hardware ( resistor values)
2022-09-20 Added debug log connection on port 24. Added Gcode tunnel fommand for configuring controller
2022-09-30 Fixes for IO configuration. First configuration for CHM36VA
2022-10-07 Added incremental moves needd for homing. Homing fully implemented
2022-10-13 Fixes in end position control ( both from inputs and soft limits)
2022-10-17 Fixes in timers and io processing
2022-10-18 Added code for GCODE validation. Not finished yet
2022-10-19 Hardware assisted pulse generation fixed
2022-10-20 Fixed G code parsing checks
2022-10-30 Fixes in pulse calculations - floating point version
2022-11-18 Fixes in movement calculation. homing procedure fixed
2022-11-22 More fixes for homing
2022-11-23 Fixed issue with 1.9.1 drivers version and stratup file
2022-11-23 Fixes in ADC, encoders
2022-11-23 Fixes in timer allocation
2022-12-01 Updated findings for future fixes
2022-12-01 Fixed rebase issues
2022-12-01 Schematics fixes - frewheeling diodes
2022-12-01 Cleanup in timers
2022-12-07 Motion blending test added
2022-12-07 1.New shield version 1.1
2023-05-22 Added pdf for schematics. Updated project files for newest Kicad
2024-10-20 New idea - mix project will take over
2024-10-20 Cleanup. Mixture project as leading one.
2024-10-20 Added hardware files
2024-10-20 Github link added to PCB texts
2025-02-07 Upadtes for Nucleo version
2025-02-12 Updated hardware design
2025-05-28 CAN FD head added
